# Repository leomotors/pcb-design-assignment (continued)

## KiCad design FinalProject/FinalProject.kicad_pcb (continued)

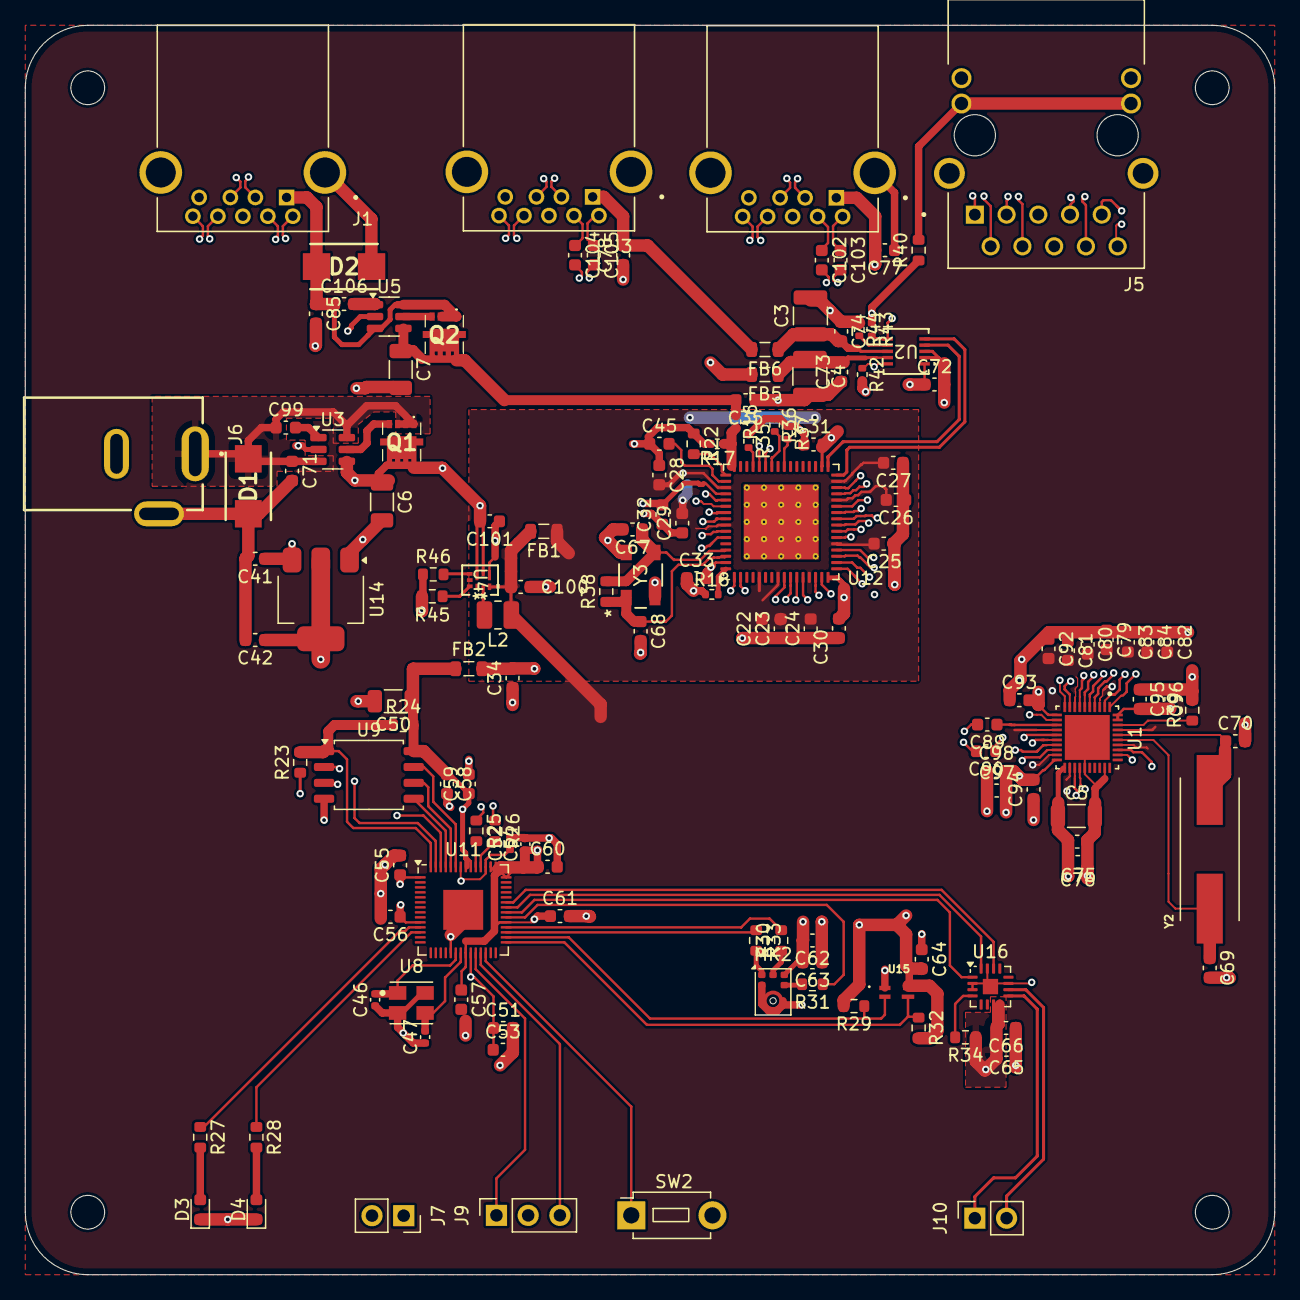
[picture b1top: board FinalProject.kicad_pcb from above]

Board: 4 copper layers, 100.0 x 100.0 mm, 143 parts (0 on the bottom side), 113 nets.

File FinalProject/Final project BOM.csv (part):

Reference,Value,Footprint,Description,Datasheet,Suppier link,Use Qty,Buy Qty,Unit price,Ext price (Use Qty * Unit price),NOTE
"C46,C47",15pF,Capacitor_SMD:C_0402_1005Metric,"15 pF ±5% 50V Ceramic Capacitor C0G, NP0 0402 (1005 Metric)",https://www.yageo.com/en/Chart/Download/pdf/CC0402JRNPO9BN150,https://www.digikey.co.th/en/products/detail/yageo/CC0402JRN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,2,1000,$0.01,$0.02,
"C67,C68",18pF,Capacitor_SMD:C_0603_1608Metric,"18 pF ±5% 50V Ceramic Capacitor C0G, NP0 0603 (1608 Metric)",https://www.yageo.com/en/Chart/Download/pdf/CC0603JRNPO9BN180,https://www.digikey.co.th/en/products/detail/yageo/CC0603JRN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,2,1000,$0.01,$0.02,
"C69,C70",27pF,Capacitor_SMD:C_0603_1608Metric,"27 pF ±5% 50V Ceramic Capacitor C0G, NP0 0603 (1608 Metric)",https://content.kemet.com/datasheets/KEM_C1003_C0G_SMD.pdf,https://www.digikey.co.th/en/products/detail/kemet/C0603C270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,2,1000,$0.01,$0.02,
C63,200pF,Capacitor_SMD:C_0603_1608Metric,200 pF ±10% 50V Ceramic Capacitor X7R 0603 (1608 Metric),https://mm.digikey.com/Volume0/opasdata/d220001/medias/docus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,https://www.digikey.co.th/en/products/detail/samsung-electro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,1,1000,$0.03,$0.03,
C76,10nF/10000pF,Capacitor_SMD:C_0603_1608Metric,10000 pF ±10% 50V Ceramic Capacitor X7R 0603 (1608 Metric),https://mm.digikey.com/Volume0/opasdata/d220001/medias/docus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,https://www.digikey.co.th/en/products/detail/samsung-electro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,1,1000,$0.00,$0.00,
"C71,C85",22nF/0.22uF,Capacitor_SMD:C_0603_1608Metric,"        
0.022 µF ±10% 25V Ceramic Capacitor X7R 0603 (1608 Metric)",https://www.we-online.com/components/products/datasheet/8850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,https://www.digikey.co.th/en/products/detail/w%C3%BCrth-elek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,2,500,$0.02,$0.04,
"C36,C37,C38,C39,C40,C51,C53,C55,C56,C57,C58,C59,C60,C61,C64,C89,C90,C102,C103,C104,C105,C22,C23,C24,C25,C26,C27,C28,C30,C31,C32,C33,C72,C73,C74,C75,C77,C78,C79,C80,C81,C82,C83,C84,C92,C93,C94,C95,C96,C97,C98,C99,C106,C62,C66",100nF/0.1uF,Capacitor_SMD:C_0603_1608Metric,"	
0.1 µF ±10% 25V Ceramic Capacitor X7R 0603 (1608 Metric)",https://mm.digikey.com/Volume0/opasdata/d220001/medias/docus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,https://www.digikey.co.th/en/products/detail/samsung-electro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,55,1000,$0.00,$0.19,
"C45,C52,C54",1uF,Capacitor_SMD:C_0603_1608Metric,"	
1 µF ±10% 25V Ceramic Capacitor X7R 0603 (1608 Metric)",https://mm.digikey.com/Volume0/opasdata/d220001/medias/docus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,https://www.digikey.co.th/en/products/detail/samsung-electro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,3,1000,$0.01,$0.03,
"C29,C34,C35,C101,C41,C42,C65",10uF,Capacitor_SMD:C_0603_1608Metric,"	
10 µF ±20% 10V Ceramic Capacitor X5R 0603 (1608 Metric)",https://weblib.samsungsem.com/mlcc/mlcc-ec-data-sheet.do?par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,https://www.digikey.co.th/en/products/detail/samsung-electro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,7,1000,$0.02,$0.12,
C100,22uF,Capacitor_SMD:C_0603_1608Metric,"        
22 µF ±20% 10V Ceramic Capacitor X5R 0603 (1608 Metric)",https://mm.digikey.com/Volume0/opasdata/d220001/medias/docus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,https://www.digikey.co.th/en/products/detail/samsung-electro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,1,1000,$0.02,$0.02,
"C5,C6,C7,C50",100uF,Capacitor_SMD:C_0603_1608Metric,"        
100 µF ±20% 6.3V Ceramic Capacitor X5R 1206 (3216 Metric)",https://mm.digikey.com/Volume0/opasdata/d220001/medias/docus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,https://www.digikey.co.th/en/products/detail/samsung-electro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,4,1000,$0.12,$0.47,there is no 0603
"C3,C4",150uF,Capacitor_SMD:C_0603_1608Metric,"        
150 µF ±20% 6.3V Ceramic Capacitor X5R 1210 (3225 Metric)",https://weblib.samsungsem.com/mlcc/mlcc-ec-data-sheet.do?par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,https://www.digikey.co.th/en/products/detail/samsung-electro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,2,100,$0.58,$1.15,there is no 0603
R24,DNF,Resistor_SMD:R_0603_1608Metric,,,,1,,,$0.00,
"R25,R26",27Ω,Resistor_SMD:R_0603_1608Metric,"27 Ohms ±5% 0.1W, 1/10W Chip Resistor 0603 (1608 Metric) Moisture Resistant Thick Film",https://www.yageo.com/upload/media/product/products/datashee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,https://www.digikey.co.th/en/products/detail/yageo/RC0603JR-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,2,1000,$0.01,$0.01,
"R30,R31,R33",51Ω,Resistor_SMD:R_0603_1608Metric,"51 Ohms ±5% 0.1W, 1/10W Chip Resistor 0603 (1608 Metric) Moisture Resistant Thick Film",https://www.yageo.com/upload/media/product/products/datashee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,https://www.digikey.co.th/en/products/detail/yageo/RC0603JR-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,3,1000,$0.01,$0.02,
"R27,R28",150Ω,Resistor_SMD:R_0603_1608Metric,"150 Ohms ±5% 0.1W, 1/10W Chip Resistor 0603 (1608 Metric) Moisture Resistant Thick Film",https://www.yageo.com/upload/media/product/products/datashee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,https://www.digikey.co.th/en/products/detail/yageo/RC0603JR-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,2,1000,$0.01,$0.01,
R40,470R,Resistor_SMD:R_0603_1608Metric,"        
470 Ohms ±5% 0.1W, 1/10W Chip Resistor 0603 (1608 Metric) Moisture Resistant Thick Film",https://www.yageo.com/upload/media/product/products/datashee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,https://www.digikey.co.th/en/products/detail/yageo/RC0603JR-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,1,1000,$0.01,$0.01,
R23,1kΩ,Resistor_SMD:R_0603_1608Metric,"1 kOhms ±5% 0.1W, 1/10W Chip Resistor 0603 (1608 Metric) Moisture Resistant Thick Film",https://www.yageo.com/upload/media/product/products/datashee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,https://www.digikey.co.th/en/products/detail/yageo/RC0603JR-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,1,1000,$0.01,$0.01,
"R29,R32",2.2kΩ,Resistor_SMD:R_0603_1608Metric,"        
2.2 kOhms ±5% 0.1W, 1/10W Chip Resistor 0603 (1608 Metric) Thick Film",https://www.yageo.com/upload/media/product/products/datashee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,https://www.digikey.co.th/en/products/detail/yageo/RC0603JR-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,2,500,$0.00,$0.01,
R39,2.49K,Resistor_SMD:R_0603_1608Metric,"2.49 kOhms ±1% 0.1W, 1/10W Chip Resistor 0603 (1608 Metric) Automotive AEC-Q200, Moisture Resistant Thick Film",https://www.yageo.com/upload/media/product/productsearch/dat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,https://www.digikey.co.th/en/products/detail/yageo/AC0603FR-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,1,1000,$0.01,$0.01,
R20,4.7k,Resistor_SMD:R_0603_1608Metric,"        
4.7 kOhms ±5% 0.1W, 1/10W Chip Resistor 0603 (1608 Metric) Automotive AEC-Q200, Moisture Resistant Thick Film",https://www.yageo.com/upload/media/product/productsearch/dat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,https://www.digikey.co.th/en/products/detail/yageo/AC0603JR-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,1,1000,$0.00,$0.00,
"R22,R35,R36,R37,R38",4.7K,Resistor_SMD:R_0402_1005Metric,"4.7 kOhms ±5% 0.063W, 1/16W Chip Resistor 0402 (1005 Metric) Thick Film",https://www.passivecomponent.com/wp-content/uploads/chipR/AS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,https://www.digikey.co.th/en/products/detail/walsin-technolo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,5,1000,$0.00,$0.01,
R18,9.53K,Resistor_SMD:R_0402_1005Metric,"9.53 kOhms ±1% 0.063W, 1/16W Chip Resistor 0402 (1005 Metric) Moisture Resistant Thick Film",https://www.yageo.com/upload/media/product/products/datashee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,https://www.digikey.co.th/en/products/detail/yageo/RC0402FR-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,1,1000,$0.00,$0.00,
"R17,R42,R43",10K,Resistor_SMD:R_0402_1005Metric,"10 kOhms ±1% 0.063W, 1/16W Chip Resistor 0402 (1005 Metric) Thick Film",https://www.passivecomponent.com/wp-content/uploads/chipR/AS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,https://www.digikey.co.th/en/products/detail/walsin-technolo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,3,1000,$0.00,$0.01,
R45,11K,Resistor_SMD:R_0603_1608Metric,"        
11 kOhms ±1% 0.1W, 1/10W Chip Resistor 0603 (1608 Metric) Thick Film",https://www.yageo.com/upload/media/product/products/datashee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,https://www.digikey.co.th/en/products/detail/yageo/RC0603FR-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,1,1000,$0.01,$0.01,
R44,25.5K,Resistor_SMD:R_0402_1005Metric,"25.5 kOhms ±1% 0.063W, 1/16W Chip Resistor 0402 (1005 Metric) Moisture Resistant Thick Film",https://www.yageo.com/upload/media/product/products/datashee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,https://www.digikey.co.th/en/products/detail/yageo/RC0402FR-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,1,1000,$0.01,$0.01,
R46,26.1K,Resistor_SMD:R_0603_1608Metric,"26.1 kOhms ±1% 0.1W, 1/10W Chip Resistor 0603 (1608 Metric) Moisture Resistant Thick Film",https://www.yageo.com/upload/media/product/products/datashee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,https://www.digikey.co.th/en/products/detail/yageo/RC0603FR-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,1,100,$0.01,$0.01,
R16,90.9K,Resistor_SMD:R_0402_1005Metric,"90.9 kOhms ±1% 0.063W, 1/16W Chip Resistor 0402 (1005 Metric) Moisture Resistant Thick Film",https://www.yageo.com/upload/media/product/products/datashee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,https://www.digikey.co.th/en/products/detail/yageo/RC0402FR-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,1,1000,$0.00,$0.00,
R19,200K,Resistor_SMD:R_0603_1608Metric,"200 kOhms ±5% 0.1W, 1/10W Chip Resistor 0603 (1608 Metric) Automotive AEC-Q200, Moisture Resistant Thick Film",https://www.yageo.com/upload/media/product/productsearch/dat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,https://www.digikey.co.th/en/products/detail/yageo/AC0603JR-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,1,1000,$0.01,$0.01,
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
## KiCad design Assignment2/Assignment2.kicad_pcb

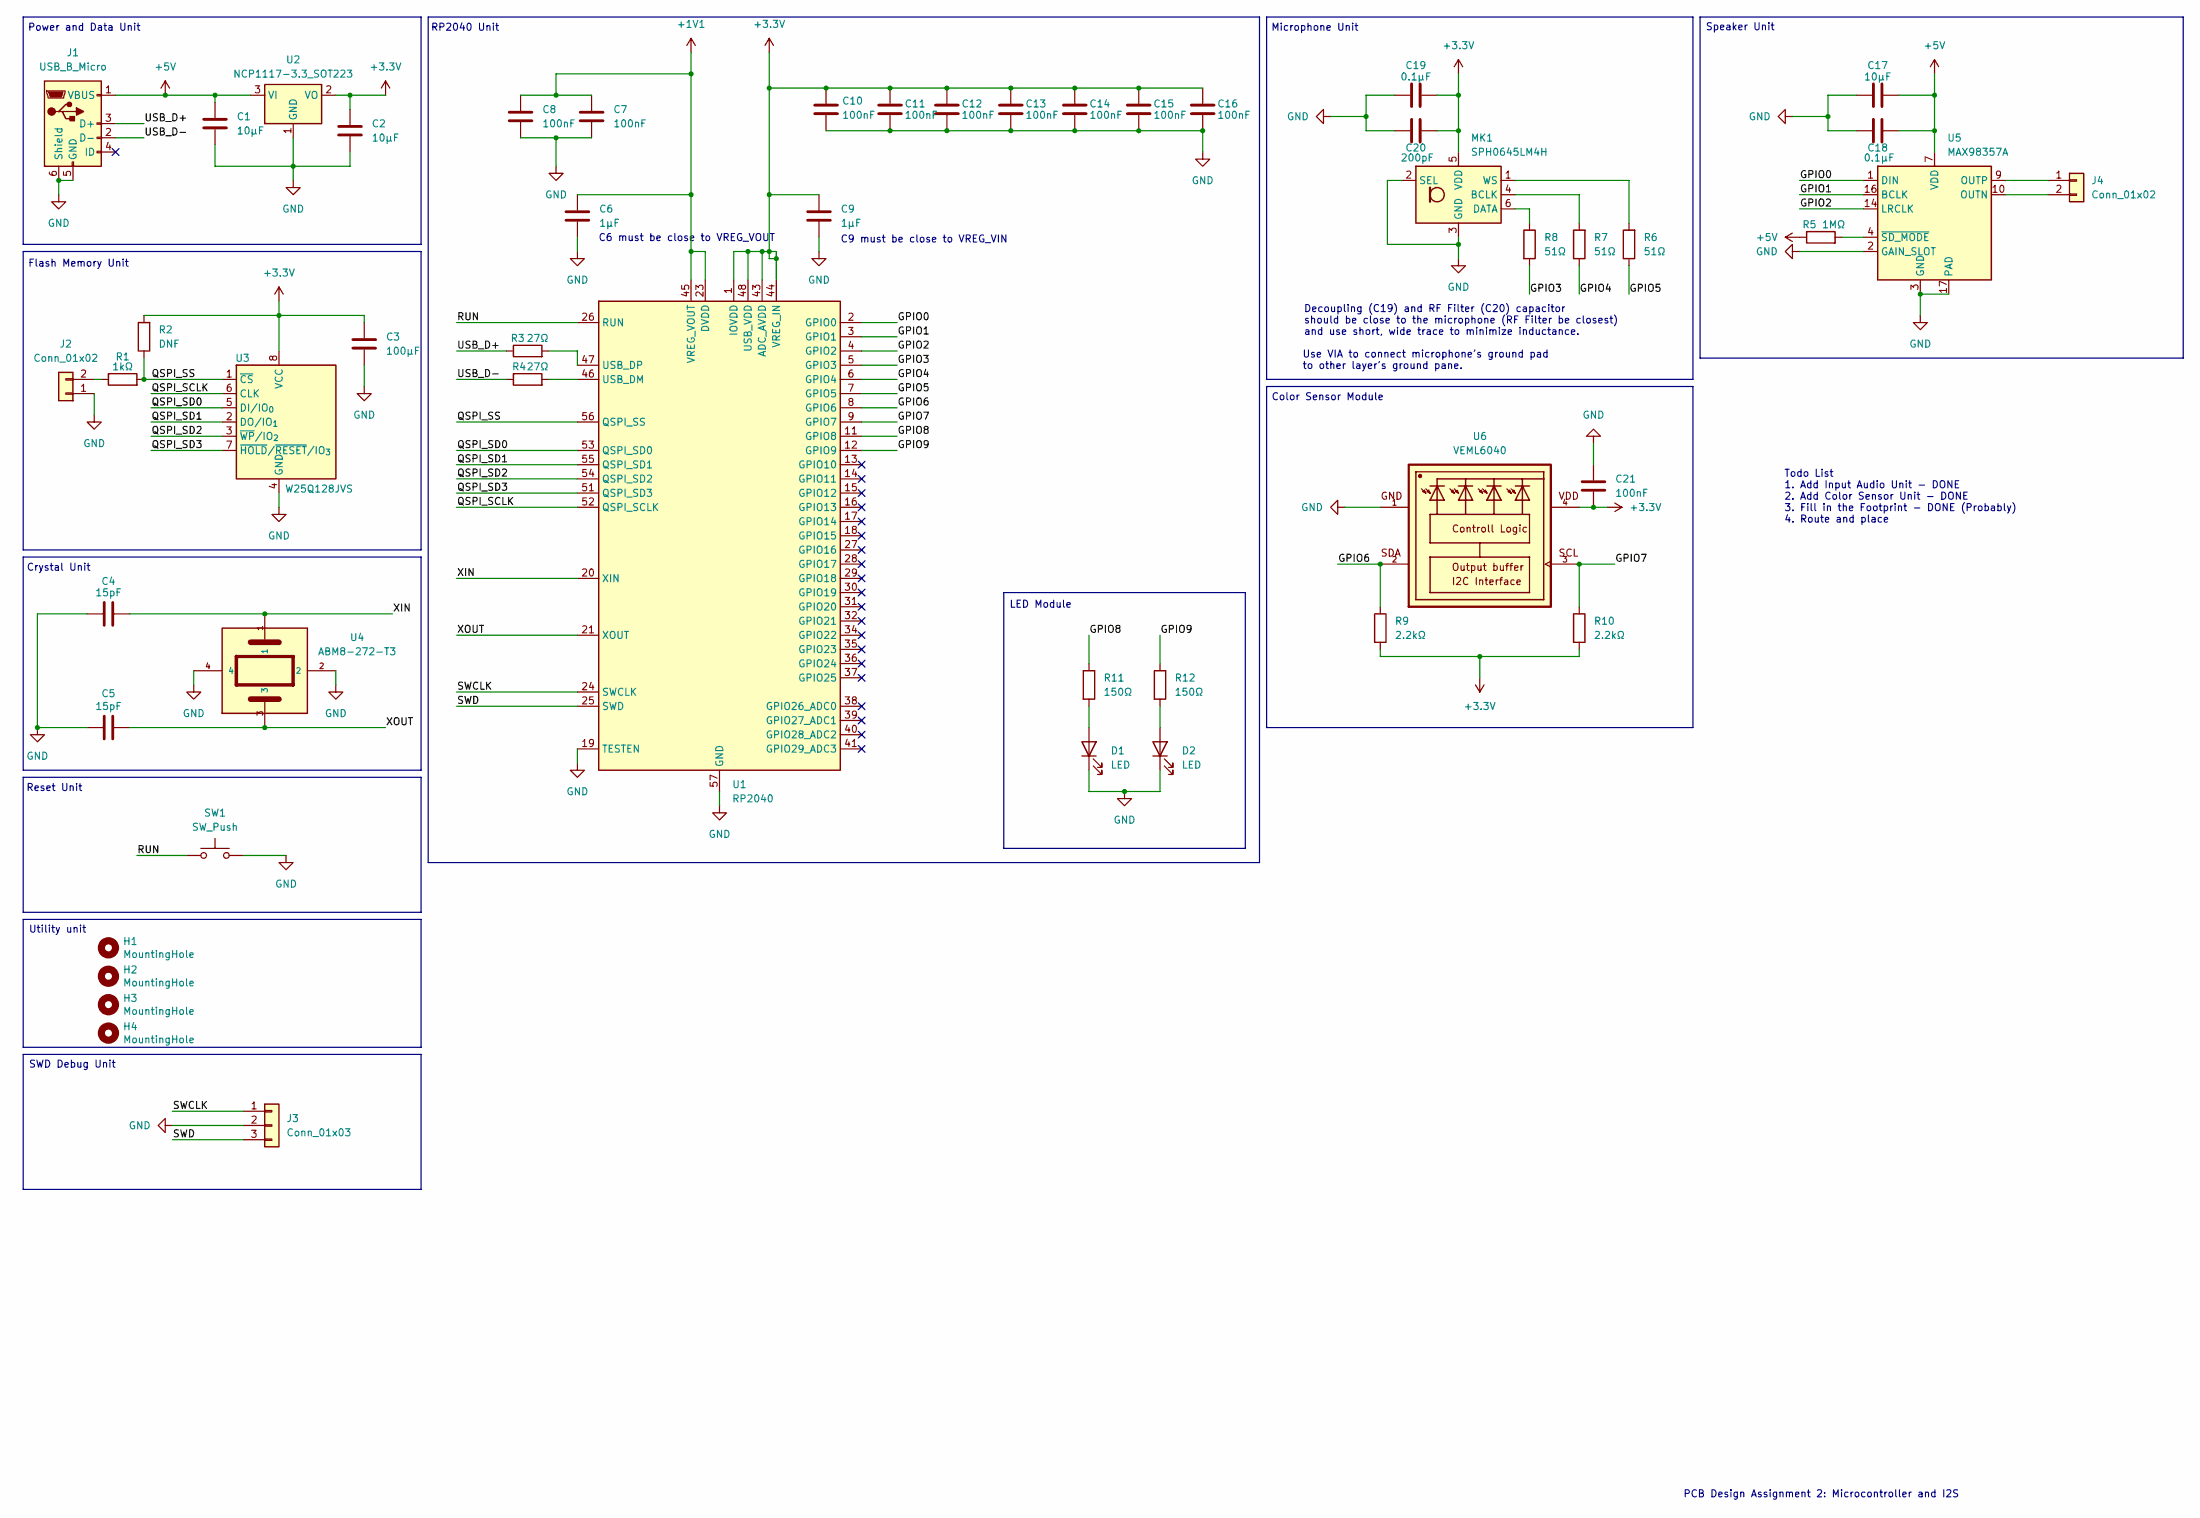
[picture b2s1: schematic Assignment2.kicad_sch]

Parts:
C1, C2, C17: 10μF; C_0603_1608Metric
C3: 100μF; C_0603_1608Metric
C4, C5: 15pF; C_0402_1005Metric
C6, C9: 1μF; C_0402_1005Metric
C7, C8, C10, C11, C12, C13, C14, C15, C16, C21: 100nF; C_0603_1608Metric
C18, C19: 0.1μF; C_0603_1608Metric
C20: 200pF; C_0603_1608Metric
D1, D2: LED; LED_0603_1608Metric
H1, H2, H3, H4: MountingHole; MountingHole_2.7mm_M2.5
J1: USB_B_Micro; USB_Micro-B_Amphenol_10103594-0001LF_Horizontal
J2, J4: Conn_01x02; PinSocket_1x02_P2.54mm_Vertical
J3: Conn_01x03; PinSocket_1x03_P2.54mm_Vertical
MK1: SPH0645LM4H; Knowles_SPH0645LM4H-6_3.5x2.65mm
R1: 1kΩ; R_0603_1608Metric
R2: DNF; R_0603_1608Metric
R3, R4: 27Ω; R_0603_1608Metric
R5: 1MΩ; R_0603_1608Metric
R6, R7, R8: 51Ω; R_0603_1608Metric
R9, R10: 2.2kΩ; R_0603_1608Metric
R11, R12: 150Ω; R_0603_1608Metric
SW1: SW_Push; SW_PUSH_1P1T_6x3.5mm_H4.3_APEM_MJTP1243
U1: RP2040; QFN-56-1EP_7x7mm_P0.4mm_EP3.2x3.2mm
U2: NCP1117-3.3_SOT223; SOT-223-3_TabPin2
U3: W25Q128JVS; SOIC-8_5.3x5.3mm_P1.27mm
U4: ABM8-272-T3
U5: MAX98357A; TQFN-16-1EP_3x3mm_P0.5mm_EP1.23x1.23mm
U6: VEML6040; VISHAY_VEML6040_1.25X2X1

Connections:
+1V1: C6.1, C7.1, C8.1, U1.23 (DVDD), U1.45 (VREG_VOUT), U1.50 (DVDD)
+3.3V: C2.1, C3.1, C9.1, C10.1, C11.1, C12.1, C13.1, C14.1, C15.1, C16.1, C19.2, C20.2, C21.2, MK1.5 (VDD), R2.2, R9.2, R10.2, U1.1 (IOVDD), U1.10 (IOVDD), U1.22 (IOVDD), U1.33 (IOVDD), U1.42 (IOVDD), U1.43 (ADC_AVDD), U1.44 (VREG_IN), U1.48 (USB_VDD), U1.49 (IOVDD), U2.2 (VO), U3.8 (VCC), U6.4
+5V: C1.1, C17.2, C18.2, J1.1 (VBUS), R5.1, U2.3 (VI), U5.7 (VDD), U5.8 (VDD)
/GPIO0: U1.2 (GPIO0), U5.1 (DIN)
/GPIO1: U1.3 (GPIO1), U5.16 (BCLK)
/GPIO2: U1.4 (GPIO2), U5.14 (LRCLK)
/GPIO3: R8.2, U1.5 (GPIO3)
/GPIO4: R7.1, U1.6 (GPIO4)
/GPIO5: R6.1, U1.7 (GPIO5)
/GPIO6: R9.1, U1.8 (GPIO6), U6.2
/GPIO7: R10.1, U1.9 (GPIO7), U6.3
/GPIO8: R11.1, U1.11 (GPIO8)
/GPIO9: R12.1, U1.12 (GPIO9)
/QSPI_SCLK: U1.52 (QSPI_SCLK), U3.6 (CLK)
/QSPI_SD0: U1.53 (QSPI_SD0), U3.5 (DI/IO_{0})
/QSPI_SD1: U1.55 (QSPI_SD1), U3.2 (DO/IO_{1})
/QSPI_SD2: U1.54 (QSPI_SD2), U3.3 (~WP/IO_{2})
/QSPI_SD3: U1.51 (QSPI_SD3), U3.7 (~HOLD/~RESET/IO_{3})
/QSPI_SS: R1.2, R2.1, U1.56 (QSPI_SS), U3.1 (~CS)
/RUN: SW1.1, U1.26 (RUN)
/SWCLK: J3.1, U1.24 (SWCLK)
/SWD: J3.3, U1.25 (SWD)
/USB_D+: J1.3 (D+), R3.1
/USB_D-: J1.2 (D-), R4.1
/XIN: C4.2, U1.20 (XIN), U4.1
/XOUT: C5.2, U1.21 (XOUT), U4.3
GND: C1.2, C2.2, C3.2, C4.1, C5.1, C6.2, C7.2, C8.2, C9.2, C10.2, C11.2, C12.2, C13.2, C14.2, C15.2, C16.2, C17.1, C18.1, C19.1, C20.1, C21.1, D1.1 (K), D2.1 (K), J1.5 (GND), J1.6 (Shield), J2.1, J3.2, MK1.2 (SEL), MK1.3 (GND), SW1.2, U1.19 (TESTEN), U1.57 (GND), U2.1 (GND), U3.4 (GND), U4.2, U4.4, U5.2 (GAIN_SLOT), U5.3 (GND), U5.11 (GND), U5.15 (GND), U5.17 (PAD), U6.1
unnamed: D1.2 (A), R11.2
unnamed: D2.2 (A), R12.2
unnamed: J2.2, R1.1
unnamed: J4.1, U5.9 (OUTP)
unnamed: J4.2, U5.10 (OUTN)
unnamed: MK1.4 (BCLK), R7.2
unnamed: MK1.6 (DATA), R8.1
unnamed: MK1.1 (WS), R6.2
unnamed: R4.2, U1.46 (USB_DM)
unnamed: R3.2, U1.47 (USB_DP)
unnamed: R5.2, U5.4 (~SD_MODE)

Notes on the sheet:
C6 must be close to VREG_VOUT
Reset Unit
Todo List 1. Add Input Audio Unit - DONE 2. Add Color Sensor Unit - DONE 3. Fill in the Footprint - DONE (Probably) 4. Route and place
PCB Design Assignment 2: Microcontroller and I2S
Power and Data Unit
Microphone Unit
C9 must be close to VREG_VIN
Decoupling (C19) and RF Filter (C20) capacitor should be close to the microphone (RF Filter be closest) and use short, wide trace to minimize inductance.
Use VIA to connect microphone's ground pad to other layer's ground pane.
RP2040 Unit
LED Module
Color Sensor Module
Flash Memory Unit
Crystal Unit
SWD Debug Unit
Utility unit
Speaker Unit

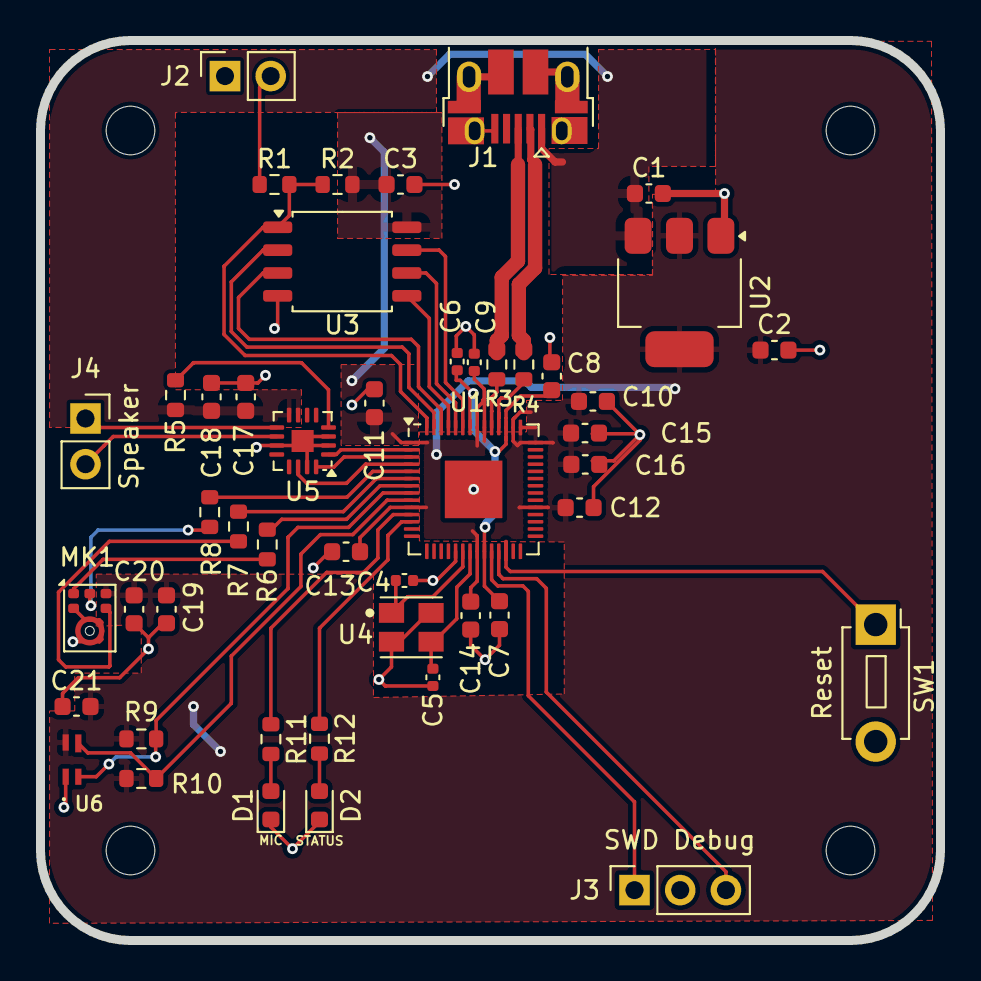
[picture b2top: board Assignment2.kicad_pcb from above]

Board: 2 copper layers, 50.0 x 50.0 mm, 51 parts (0 on the bottom side), 38 nets.

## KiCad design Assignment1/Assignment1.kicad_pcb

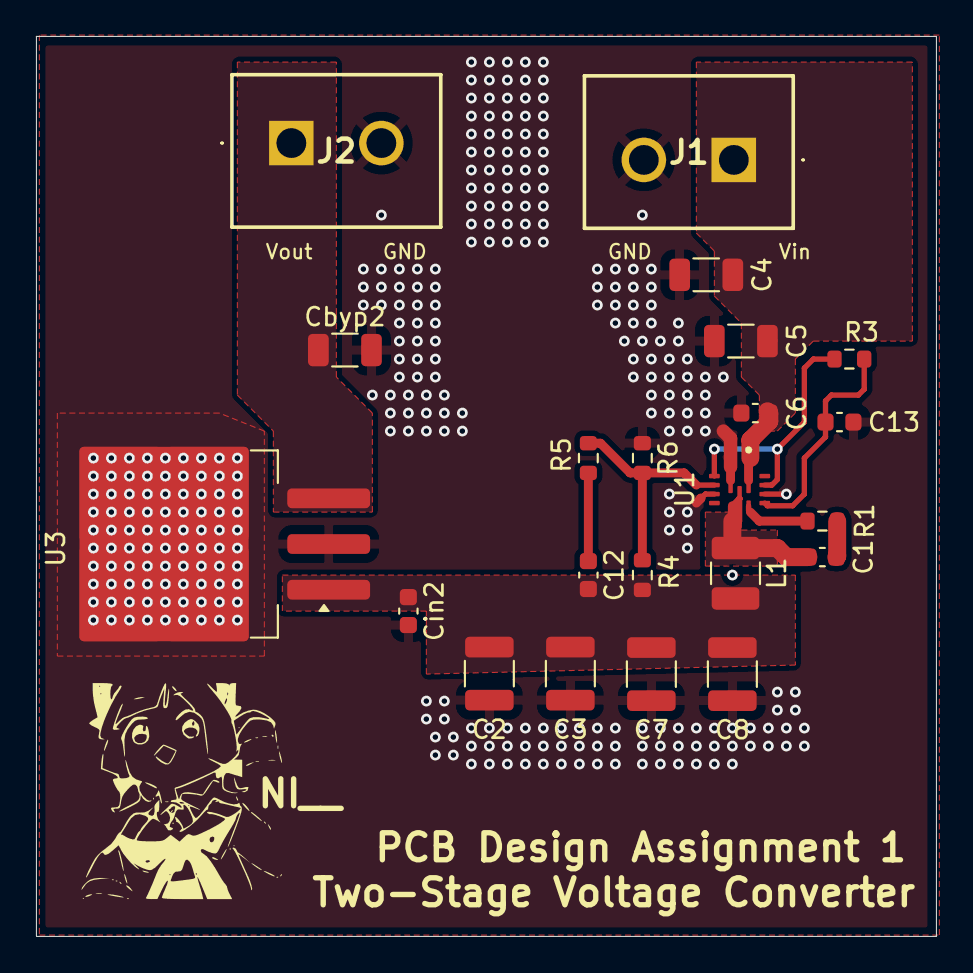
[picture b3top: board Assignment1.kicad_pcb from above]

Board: 2 copper layers, 50.0 x 50.0 mm, 22 parts (0 on the bottom side), 11 nets.

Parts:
C1, C6: 0.1μF; C_0603_1608Metric
C2, C3, C7, C8: 22μF; C_1210_3225Metric
C4, C5: 10μF; C_1206_3216Metric
C12: 22pF; C_0603_1608Metric
C13: 1μF; C_0603_1608Metric
Cbyp2: 47μF; C_1206_3216Metric
Cin2: 1μF; C_0603_1608Metric
J1, J2: Conn_01x02_Pin; 5EHDVC02P
L1: 1.5μH; L_1210_3225Metric
R1, R5: 0; R_0603_1608Metric
R3: 100k; R_0603_1608Metric
R4: 110k; R_0603_1608Metric
R6: 20k; R_0603_1608Metric
U1: TPS51386RJNR; VREG_TPS51386RJNR
U3: TO-263-3_TabPin2

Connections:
/BuckStep_Vout: C2.1, C3.1, C7.1, C8.1, C12.2, Cin2.1, L1.2, R4.2, U3.1 (VIN)
/Buck_FB: R4.1, R5.1, R6.2, U1.4 (FB)
/Buck_PG: R3.2, U1.3 (PG), U1.11 (EN)
/Buck_SW: C1.2, L1.1, U1.7 (SW)
/Buck_VBST: R1.1, U1.8 (VBST)
/Buck_Vcc: C13.1, R3.1, U1.9 (VCC)
/Buck_Vin: C4.1, C5.1, C6.1, J1.1, U1.1 (VIN)
/Vout: Cbyp2.1, J2.1, U3.3 (VOUT)
Earth: C2.2, C3.2, C4.2, C5.2, C6.2, C7.2, C8.2, C13.2, Cbyp2.2, Cin2.2, J1.2, J2.2, R6.1, U1.2 (PGND), U1.5 (SS), U1.10 (AGND), U3.2 (GND)
unnamed: C1.1, R1.2
unnamed: C12.1, R5.2

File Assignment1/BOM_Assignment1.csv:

Reference,Value,Datasheet,Footprint,Qty,DNP,Description,Suppiler link,Price per unit,Note
"C1,C6",0.1uF,https://mm.digikey.com/Volume0/opasdata/d220001/medias/docus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,Capacitor_SMD:C_0603_1608Metric,10,,0.1 µF ±10% 50V Ceramic Capacitor X7R 0603 (1608 Metric),https://www.digikey.co.th/en/products/detail/samsung-electro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,$0.02,Actual Qty = 2 but buying as 10 is equally cheap.
"C2,C3,C7,C8",22uF,https://mm.digikey.com/Volume0/opasdata/d220001/medias/docus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,Capacitor_SMD:C_1210_3225Metric,4,,22 µF ±10% 25V Ceramic Capacitor X7R 1210 (3225 Metric),https://www.digikey.co.th/en/products/detail/samsung-electro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,$0.54,
"C4,C5",10uF,https://mm.digikey.com/Volume0/opasdata/d220001/medias/docus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,Capacitor_SMD:C_1206_3216Metric,2,,10 µF ±10% 25V Ceramic Capacitor X7R 1206 (3216 Metric),https://www.digikey.co.th/en/products/detail/samsung-electro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,$0.17,
C12,22pF,https://content.kemet.com/datasheets/KEM_C1003_C0G_SMD.pdf,Capacitor_SMD:C_0603_1608Metric,1,,"22 pF ±10% 25V Ceramic Capacitor C0G, NP0 0603 (1608 Metric)",https://www.digikey.co.th/en/products/detail/kemet/C0603C220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,$0.10,
"C13,Cin2",1uF,https://mm.digikey.com/Volume0/opasdata/d220001/medias/docus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,Capacitor_SMD:C_0603_1608Metric,10,,1 µF ±10% 25V Ceramic Capacitor X7R 0603 (1608 Metric),https://www.digikey.co.th/en/products/detail/samsung-electro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,$0.03,Actual Qty = 2 but buying as 10 is equally cheap.
Cbyp2,47uF,https://datasheets.kyocera-avx.com/TLJ.pdf,Capacitor_SMD:C_1206_3216Metric,1,,"	
47 µF Molded Tantalum Capacitors 10 V 1206 (3216 Metric) 600mOhm",https://www.digikey.co.th/en/products/detail/kyocera-avx/TLJ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,$0.72,
"J1,J2",Conn_01x02_Pin,https://www.es.co.th/Schemetic/PDF/5EHDVC.PDF,5EHDVC-02P-KiCad:5EHDVC02P,2,,"
Plug-in Terminal Block 2pins,Male,300V/15A Pitch 5.00mm",https://www.es.co.th/detail.asp?Prod=000501133,$0.17,
L1,1.5uH,https://search.murata.co.jp/Ceramy/image/img/P02/J(E)TE243A-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,Inductor_SMD:L_1210_3225Metric,1,,"	
1.5 µH Shielded Drum Core, Wirewound Inductor 3 A 48mOhm Max 1210 (3225 Metric)",https://www.digikey.co.th/en/products/detail/murata-electron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,$0.55,
"R1,R5",0,https://industrial.panasonic.com/cdbs/www-data/pdf/RDA0000/A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,Resistor_SMD:R_0603_1608Metric,10,,0 Ohms Jumper Chip Resistor 0603 (1608 Metric) Automotive AEC-Q200 Thick Film,https://www.digikey.co.th/en/products/detail/panasonic-elect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,$0.03,Actual Qty = 2 but buying as 10 is equally cheap.
R3,100k,https://industrial.panasonic.com/cdbs/www-data/pdf/RDA0000/A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,Resistor_SMD:R_0603_1608Metric,1,,"	
100 kOhms ±1% 0.1W, 1/10W Chip Resistor 0603 (1608 Metric) Automotive AEC-Q200 Thick Film",https://www.digikey.co.th/en/products/detail/panasonic-elect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,$0.10,
R4,110k,https://www.vishay.com/docs/28773/crcwce3.pdf,Resistor_SMD:R_0603_1608Metric,1,,"110 kOhms ±1% 0.1W, 1/10W Chip Resistor 0603 (1608 Metric) Thick Film",https://www.digikey.co.th/en/products/detail/vishay-dale/CRC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,$0.10,
R6,20k,https://industrial.panasonic.com/cdbs/www-data/pdf/RDA0000/A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,Resistor_SMD:R_0603_1608Metric,1,,"20 kOhms ±1% 0.1W, 1/10W Chip Resistor 0603 (1608 Metric) Automotive AEC-Q200 Thick Film",https://www.digikey.co.th/en/products/detail/panasonic-elect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,$0.10,
U1,TPS51386RJNR,https://www.ti.com/lit/ds/symlink/tps51386.pdf?ts=1703257830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,TPS51386RJNR:VREG_TPS51386RJNR,1,,"	
Buck Switching Regulator IC Positive Adjustable 4.5V to 24V Input, 8A",https://www.digikey.co.th/en/products/detail/texas-instrumen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,$0.78,
U3,~,https://www.lcsc.com/datasheet/lcsc_datasheet_2409291004_HTC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,Package_TO_SOT_SMD:TO-263-3_TabPin2,1,,"3A Fixed 3.3V Positive electrode 20V TO-263-3 Voltage Regulators - Linear, Low Drop Out (LDO) Regulators ROHS",https://www.lcsc.com/product-detail/Others_HTC-Korea-TAEJIN-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,$0.92,
,,,,,,,,,
,,,,,,,Total cost,$6.96,

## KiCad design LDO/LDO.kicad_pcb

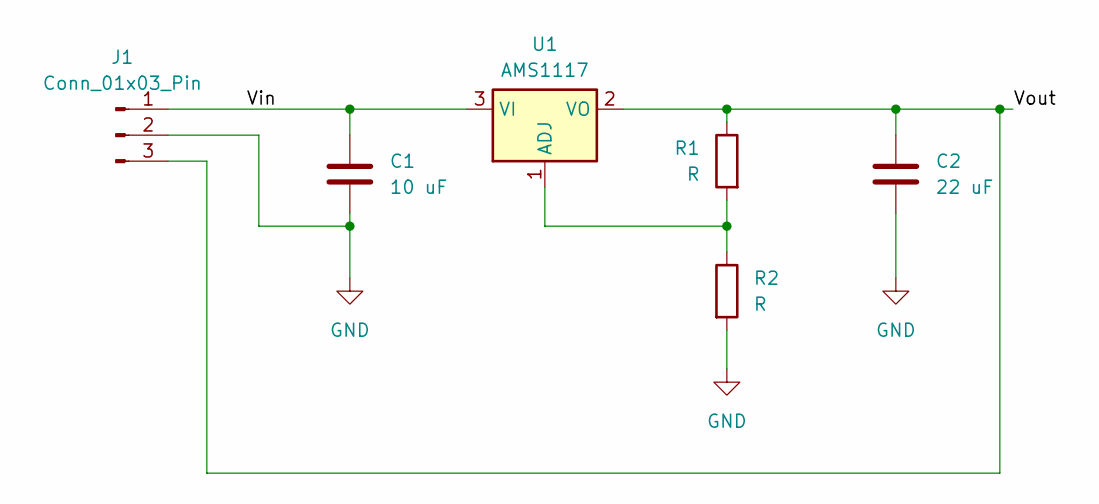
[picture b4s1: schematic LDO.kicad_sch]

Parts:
C1: 10 uF; C_0603_1608Metric
C2: 22 uF; C_0603_1608Metric
J1: Conn_01x03_Pin; PinHeader_1x03_P2.54mm_Vertical
R1, R2: R; R_0603_1608Metric
U1: AMS1117; SOT-223-3_TabPin2

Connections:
/Vin: C1.1, J1.1, U1.3 (VI)
/Vout: C2.1, J1.3, R1.1, U1.2 (VO)
GND: C1.2, C2.2, J1.2, R2.2
unnamed: R1.2, R2.1, U1.1 (ADJ)

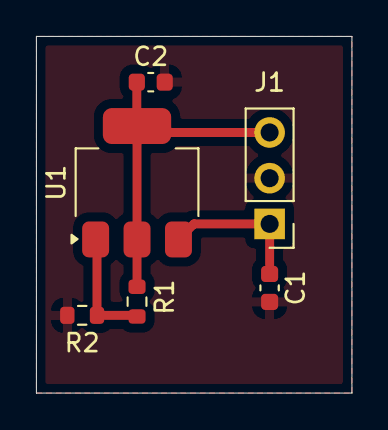
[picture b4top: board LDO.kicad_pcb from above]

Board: 2 copper layers, 17.5 x 19.8 mm, 6 parts (0 on the bottom side), 4 nets.

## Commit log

2025-01-26 initial commit: assignment 1
2025-01-30 First Assignment
2025-01-30 fix version
2025-01-30 update gitignore
2025-02-03 Update Assignment 1
2025-02-03 fix smt
2025-02-03 generate BOM
2025-02-03 fix typo and update pcb
2025-02-03 reformat
2025-02-03 regenerate BOM
2025-02-03 update C 22pf package size to 0603
2025-02-04 assignment1, schematic: update label
2025-02-04 assignment1: route pcb
2025-02-04 as1: reroute stuff
2025-02-04 as1: momoi silkscreen and update bom
2025-02-06 add vias and copper zone as solid
2025-02-06 Add silk screen for Vin, Vout and update track angle to 45
2025-02-06 R1 C1 route
2025-02-06 move lib to inside project
2025-02-06 make LDO copper plane solid
2025-02-06 remove Assignment1.csv
2025-02-06 block diagram
2025-03-17 Init Assignment 2
2025-03-18 assignment2: microphone and color module
2025-03-18 assignment2: add leds
2025-03-18 assignment2: complete schematic
2025-03-19 route
2025-03-20 swap c19 and c20, add silkscreen and round corner
2025-03-20 fix DRC
2025-03-20 update led silk screen
2025-03-20 move capacitors closer to 3.3v and 1.1v pin and reduce diff length of usb differential pair
2025-03-20 curve wire
2025-03-20 footprint
2025-04-10 fix route
2025-04-19 copy assignment 2 to template for final project
2025-04-19 FinalProject Init
2025-04-27 Final Project Schematic
2025-04-27 fix schematic
2025-04-27 fix footprint
2025-04-29 route pi part 1
2025-05-01 checkpoint
2025-05-01 checkpoint 2
2025-05-01 help
2025-05-02 update big capacitors footprint to use bigger than 0603
2025-05-02 connected all components but having DRC error
2025-05-02 having DRC error
2025-05-02 fix vias error
2025-05-09 increase via hole diameter
